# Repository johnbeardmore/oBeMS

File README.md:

oBeMS
=====

Open source environmental monitoring, automatic meter reading and building management system.

Note that the items in [square brackets] below are planned, but not yet implemented.

Open Source GPL2 system for energy and environmental measurement, automatic meter reading (AMR), [building energy management (BEMS), and building management (BMS)].

The system consists of server processes which provide access to sensors and actuators via IP address and port number. Server processes are used which provide user interfaces, [make BMS and BEMS decisions], and relay information to archival stores.

An archival store is provided to record environmental conditions, [and BMS and BEMS decisions].

Modules can be distributed around the internet, and in this sense it may be seen as part of the Internet Of Things (IoT).

Initial development has mostly taken place on the Raspberry Pi under Raspbian, though it should port perfectly well to other linux based boards, e.g. the BeagleBone.

The archival database has been implemented on an Intel Linux box to avoid doing frequent writes to SD cards.

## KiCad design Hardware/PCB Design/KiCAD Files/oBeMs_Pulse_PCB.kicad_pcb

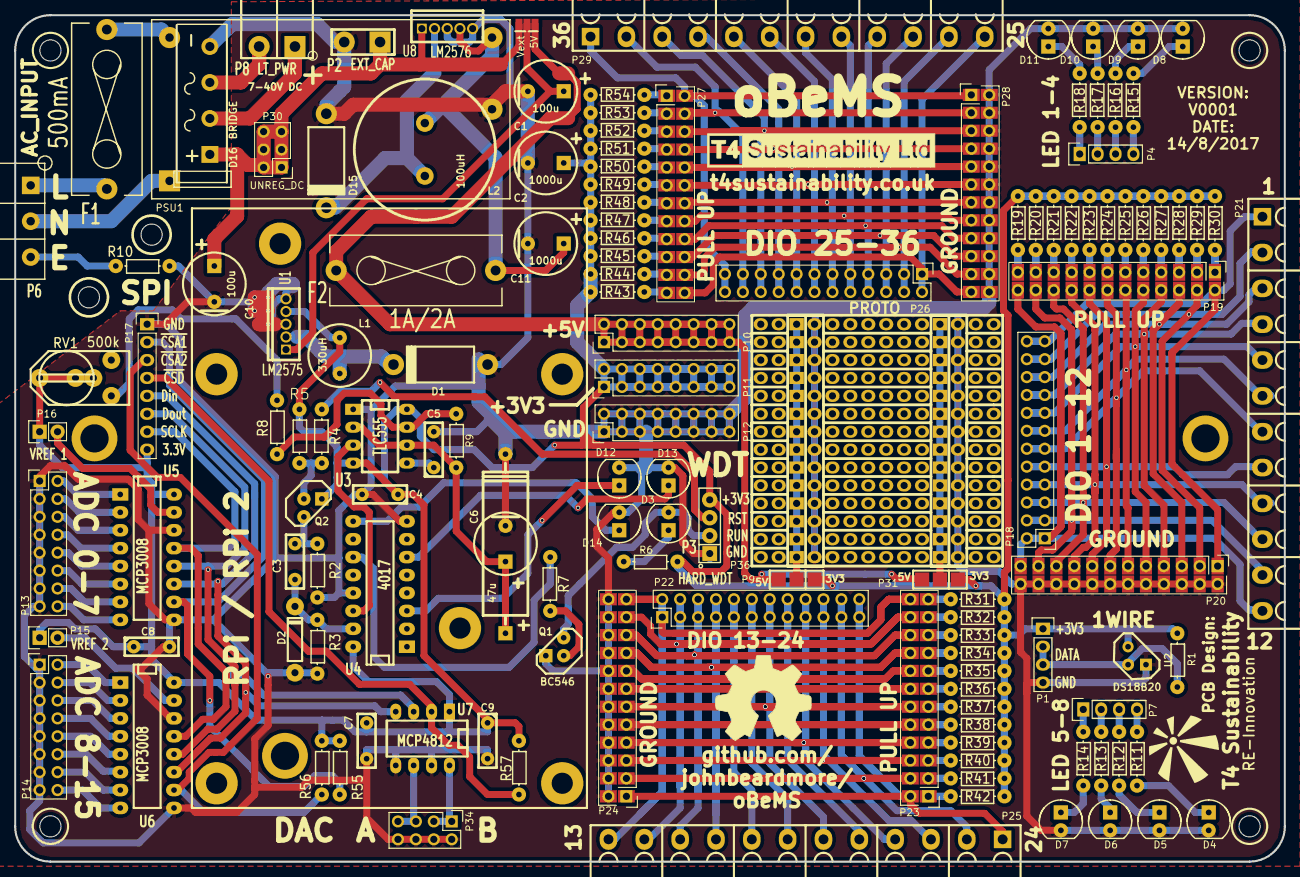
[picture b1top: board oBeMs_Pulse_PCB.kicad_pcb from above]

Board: 2 copper layers, 180.0 x 120.0 mm, 140 parts (0 on the bottom side), 147 nets.

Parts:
C1, C10: 100u; C2V8_V
C2, C11: 1000u; C2V8_V
C3, C4, C5, C7, C8, C9: 1u; C1_wide_lg_pad_2
C6: 47u; C2V8_VandA
CPU1: RPi_B; RPi_B_B+_MOUNTING
D1, D15: 1N5822; TH_Diode_DO-201AD
D2: 1N4001; TH_Diode_1
D3: RED; LED-5MM_larg_pad
D4, D5, D6, D7, D8, D9, D10, D11: LED; LED-5MM_larg_pad
D12: GRN; LED-5MM_larg_pad
D13: YEL; LED-5MM_larg_pad
D14: ORG; LED-5MM_larg_pad
D16: BRIDGE; TH_BridgeRect_8A
F1: 500mA; TH_Fuse_Holder_5-20_CPC
F2: 1A/2A; TH_Fuse_Holder_5-20_CPC
H1, H2: AC Cover Mount Hole; 3mm_hole
L1: 330uH; TH_Inductor
L2: 100uH; TH_Inductor_ELC18B101L
LG1: REI Logo; reinnovation_logo_15mm
LG2: T4 Logo; T4_32mm
LG3: OSHW Logo; OSHW_13mm
P1: 1WIRE; Pin_Header_Straight_1x04
P2: EXT_CAP; SIL-2_LG_PAD
P3: HARD_WDT; TH_4x1_CONN
P4: LED 5-8; Pin_Header_Straight_1x04
P6: AC_INPUT; TH_3W_CamdenBoss
P7: LED 1-4; Pin_Header_Straight_1x04
P8: LT_PWR; TH_CONN_2W_LGPAD
P9: V1?; SIL-3_solder_connect
P10: 5V; Pin_Header_Straight_2x08
P11: 3V3; Pin_Header_Straight_2x08
P12: GND; Pin_Header_Straight_2x08
P13: ADC_0-7; Pin_Header_Straight_2x08
P14: ADC_8-15; Pin_Header_Straight_2x08
P15: ADC_VREF_2; Pin_Header_Straight_1x02
P16: ADC_VREF_1; Pin_Header_Straight_1x02
P17: SPI_ADC_DAC; Pin_Header_Straight_1x08
P18, P22, P26: DIO_OUTPUT; Pin_Header_Straight_2x12
P19, P23, P27: PULL_UP; Pin_Header_Straight_2x12_SM_Connect
P20, P24, P28: GROUND; Pin_Header_Straight_2x12_SM_Connect
P21, P25, P29: DIO_INPUT; HEADER_12Way_Wiedermuller_SX
P30: UNREG_DC; Pin_Header_Straight_2x03
P31: V2?; SIL-3_solder_connect
P32: V_PWR; SM_3pad_SOLDER_named
P34: DAC; Pin_Header_Straight_2x04
P36: PROTOTYPING_AREA; PROTO_AREA_16x14
PCB1: PCB; PCB_120x150_WISKA
PSU1: PSU_10W_5V; TH_DCDC_PowerPac_5W_10W
Q1: BC546; TO92-PNP_large_pad
Q2: BC556; TO92-PNP_large_pad
R1: 4k7; TH_Resistor_1
R2, R8, R9: 10k; TH_Resistor_1
R3, R10: 1M; TH_Resistor_1
R4, R7: 1k; TH_Resistor_1
R5: 39k; TH_Resistor_1
R6: 100; TH_Resistor_1
R11, R12, R13, R14, R15, R16, R17, R18, R19, R20, R21, R22, R23, R24, R25, R26, R27, R28, R29, R30, R31, R32, R33, R34, R35, R36, R37, R38, R39, R40, R41, R42, R43, R44, R45, R46, R47, R48, R49, R50, R51, R52, R53, R54: 120; TH_Resistor_1
R55, R56, R57: 100k; TH_Resistor_1
RV1: 500k; RV_various_lg_pad
U1: LM2575; TO220_5PIN
U2: DS18B20; TO92_DS18B20
U3: TLC555; DIP-8__300_ELL
U4: 4017; DIP-16__300_ELL_lg_pad
U5, U6: MCP3008; DIP-16__300_ELL_lg_pad
U7: MCP4812; DIP-8_300_ELL
U8: LM2576; TO220_5PIN

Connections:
+3.3V: C2.1, C4.1, C7.1, C8.1, C9.1, L1.2, P1.1, P3.4, P9.1, P11.1, P11.2, P11.3, P11.4, P11.5, P11.6, P11.7, P11.8, P11.9, P11.10, P11.11, P11.12, P11.13, P11.14, P11.15, P11.16, P15.1, P16.1, P17.8, P31.1, Q2.3, R1.1, R5.1, R6.1, R19.1, R20.1, R21.1, R22.1, R23.1, R24.1, R25.1, R26.1, R27.1, R28.1, R29.1, R30.1, R31.1, R32.1, R33.1, R34.1, R35.1, R36.1, R37.1, R38.1, R39.1, R40.1, R41.1, R42.1, R43.1, R44.1, R45.1, R46.1, R47.1, R48.1, R49.1, R50.1, R51.1, R52.1, R53.1, R54.1, R55.1, R56.1, R57.1, RV1.2, U1.4, U2.3, U3.4, U3.8, U4.16, U5.16, U6.16, U7.1
+5V: F2.2, P9.3, P10.1, P10.2, P10.3, P10.4, P10.5, P10.6, P10.7, P10.8, P10.9, P10.10, P10.11, P10.12, P10.13, P10.14, P10.15, P10.16, P31.3, P32.3
/LED IO/LED0: P7.4, R11.1
/LED IO/LED1: P7.3, R12.1
/LED IO/LED2: P7.2, R13.1
/LED IO/LED3: P7.1, R14.1
/LED IO/LED4: P4.4, R15.1
/LED IO/LED5: P4.3, R16.1
/LED IO/LED6: P4.2, R17.1
/LED IO/LED7: P4.1, R18.1
/PowerSupply/L: F1.1, P6.1
/PowerSupply/N: P6.2, PSU1.1
/PowerSupply/VIN_A: D16.4, P8.1
/PowerSupply/VIN_B: D16.2, P8.2
/TemperatureSensor/D-1-Wire: P1.2, P1.3, R1.2, U2.2
/Watch Dog Timer/WDT_IN: P3.3, R4.2
/Watch Dog Timer/WDT_OUT: D3.2, P3.2, Q1.1
GND: C1.2, C2.2, C4.2, C5.2, C6.2, C7.2, C8.2, C9.2, C10.2, C11.2, D1.1, D2.1, D4.2, D5.2, D6.2, D7.2, D8.2, D9.2, D10.2, D11.2, D12.2, D13.2, D14.2, D15.1, D16.1, P1.4, P2.2, P3.1, P12.1, P12.2, P12.3, P12.4, P12.5, P12.6, P12.7, P12.8, P12.9, P12.10, P12.11, P12.12, P12.13, P12.14, P12.15, P12.16, P13.1, P13.3, P13.5, P13.7, P13.9, P13.11, P13.13, P13.15, P14.1, P14.3, P14.5, P14.7, P14.9, P14.11, P14.13, P14.15, P17.1, P20.2, P20.4, P20.6, P20.8, P20.10, P20.12, P20.14, P20.16, P20.18, P20.20, P20.22, P20.24, P24.2, P24.4, P24.6, P24.8, P24.10, P24.12, P24.14, P24.16, P24.18, P24.20, P24.22, P24.24, P28.2, P28.4, P28.6, P28.8, P28.10, P28.12, P28.14, P28.16, P28.18, P28.20, P28.22, P28.24, P34.2, P34.4, P34.6, P34.8, P36.2, P36.18, PSU1.4, Q1.3, R2.2, R3.2, R10.1, U1.3, U1.5, U2.1, U3.1, U4.8, U4.13, U5.9, U5.14, U6.9, U6.14, U7.5, U7.7, U8.3, U8.5
GNDPWR: P6.3, R10.2
unnamed: C1.1, P32.2, U1.1
unnamed: C3.1, Q2.1, R2.1
unnamed: C3.2, D2.2, R3.1, U4.15
unnamed: C5.1, U3.5
unnamed: C6.1, R9.2, U3.2, U3.6
unnamed: C10.1, D16.3, P2.1, P30.1, P30.2, P30.3, P30.4, P30.5, P30.6, P32.1, U8.1
unnamed: C11.1, F2.1, L2.2, PSU1.3, U8.4
unnamed: D1.2, L1.1, U1.2
unnamed: D3.1, R6.2
unnamed: D4.1, R11.2
unnamed: D5.1, R12.2
unnamed: D6.1, R13.2
unnamed: D7.1, R14.2
unnamed: D8.1, R15.2
unnamed: D9.1, R16.2
unnamed: D10.1, R17.2
unnamed: D11.1, R18.2
unnamed: D12.1, U4.3
unnamed: D13.1, U4.6
unnamed: D14.1, U4.9
unnamed: D15.2, L2.1, U8.2
unnamed: F1.2, PSU1.2
unnamed: P13.2, U5.1
unnamed: P13.4, U5.2
unnamed: P13.6, U5.3
unnamed: P13.8, U5.4
unnamed: P13.10, U5.5
unnamed: P13.12, U5.6
unnamed: P13.14, U5.7
unnamed: P13.16, U5.8
unnamed: P14.2, U6.1
unnamed: P14.4, U6.2
unnamed: P14.6, U6.3
unnamed: P14.8, U6.4
unnamed: P14.10, U6.5
unnamed: P14.12, U6.6
unnamed: P14.14, U6.7
unnamed: P14.16, U6.8
unnamed: P15.2, U6.15
unnamed: P16.2, U5.15
unnamed: P17.2, R55.2, U5.10
unnamed: P17.3, R56.2, U6.10
unnamed: P17.4, R57.2, U7.2
unnamed: P17.5, U5.11, U6.11, U7.4
unnamed: P17.6, U5.12, U6.12
unnamed: P17.7, U5.13, U6.13, U7.3
unnamed: P18.1, P18.2, P19.24, P20.23, P21.12
unnamed: P18.3, P18.4, P19.22, P20.21, P21.11
unnamed: P18.5, P18.6, P19.20, P20.19, P21.10
unnamed: P18.7, P18.8, P19.18, P20.17, P21.9
unnamed: P18.9, P18.10, P19.16, P20.15, P21.8
unnamed: P18.11, P18.12, P19.14, P20.13, P21.7
unnamed: P18.13, P18.14, P19.12, P20.11, P21.6
unnamed: P18.15, P18.16, P19.10, P20.9, P21.5
unnamed: P18.17, P18.18, P19.8, P20.7, P21.4
unnamed: P18.19, P18.20, P19.6, P20.5, P21.3
unnamed: P18.21, P18.22, P19.4, P20.3, P21.2
unnamed: P18.23, P18.24, P19.2, P20.1, P21.1
unnamed: P19.1, R30.2
unnamed: P19.3, R29.2
unnamed: P19.5, R28.2
unnamed: P19.7, R27.2
unnamed: P19.9, R26.2
unnamed: P19.11, R25.2
unnamed: P19.13, R24.2
unnamed: P19.15, R23.2
unnamed: P19.17, R22.2
unnamed: P19.19, R21.2
unnamed: P19.21, R20.2
unnamed: P19.23, R19.2
unnamed: P22.1, P22.2, P23.24, P24.23, P25.12
unnamed: P22.3, P22.4, P23.22, P24.21, P25.11
unnamed: P22.5, P22.6, P23.20, P24.19, P25.10
unnamed: P22.7, P22.8, P23.18, P24.17, P25.9
unnamed: P22.9, P22.10, P23.16, P24.15, P25.8
unnamed: P22.11, P22.12, P23.14, P24.13, P25.7
unnamed: P22.13, P22.14, P23.12, P24.11, P25.6
unnamed: P22.15, P22.16, P23.10, P24.9, P25.5
unnamed: P22.17, P22.18, P23.8, P24.7, P25.4
unnamed: P22.19, P22.20, P23.6, P24.5, P25.3
unnamed: P22.21, P22.22, P23.4, P24.3, P25.2
unnamed: P22.23, P22.24, P23.2, P24.1, P25.1
unnamed: P23.1, R42.2
unnamed: P23.3, R41.2
unnamed: P23.5, R40.2
unnamed: P23.7, R39.2
unnamed: P23.9, R38.2
unnamed: P23.11, R37.2
unnamed: P23.13, R36.2
unnamed: P23.15, R35.2
unnamed: P23.17, R34.2
unnamed: P23.19, R33.2
unnamed: P23.21, R32.2
unnamed: P23.23, R31.2
unnamed: P26.1, P26.2, P27.24, P28.23, P29.12
unnamed: P26.3, P26.4, P27.22, P28.21, P29.11
unnamed: P26.5, P26.6, P27.20, P28.19, P29.10
unnamed: P26.7, P26.8, P27.18, P28.17, P29.9
unnamed: P26.9, P26.10, P27.16, P28.15, P29.8
unnamed: P26.11, P26.12, P27.14, P28.13, P29.7
unnamed: P26.13, P26.14, P27.12, P28.11, P29.6
unnamed: P26.15, P26.16, P27.10, P28.9, P29.5
unnamed: P26.17, P26.18, P27.8, P28.7, P29.4
unnamed: P26.19, P26.20, P27.6, P28.5, P29.3
unnamed: P26.21, P26.22, P27.4, P28.3, P29.2
unnamed: P26.23, P26.24, P27.2, P28.1, P29.1
unnamed: P27.1, R54.2
unnamed: P27.3, R53.2
unnamed: P27.5, R52.2
unnamed: P27.7, R51.2
unnamed: P27.9, R50.2
unnamed: P27.11, R49.2
unnamed: P27.13, R48.2
unnamed: P27.15, R47.2
unnamed: P27.17, R46.2
unnamed: P27.19, R45.2
unnamed: P27.21, R44.2
unnamed: P27.23, R43.2
unnamed: P31.2, P36.17
unnamed: P34.1, P34.3, U7.8
unnamed: P34.5, P34.7, U7.6
unnamed: P9.2, P36.1
unnamed: Q1.2, R7.1
unnamed: Q2.2, R4.1, R5.2
unnamed: R7.2, U4.11
unnamed: R8.1, RV1.1
unnamed: R8.2, R9.1, U3.7
unnamed: U3.3, U4.14

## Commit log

2015-10-06 Initial commit of PCB Schematic
2015-10-12 Update Schematic and add presentation
2015-10-22 Update Schematic WDT and PSU
2015-11-04 Update to initial version of PCB
    Initial PCB version.
2015-11-09 Update PCB
    With notes from John
2015-12-17 Version 3 revision
    Added 3A switching 5V supply and Capacitors axial and radial
2015-12-19 Updated small changes.
    Info and changes from email 18/12/15.
2015-12-20 Small changes on PCB
2015-12-21 Updates from email 21/12/15
2015-12-22 More small changes 22/12/15
2015-12-23 Rev 6. Final changes before PCB v0000 done
2017-08-14 Changes for v0001
    Multiple PCb changes. 50Pcs ordered
